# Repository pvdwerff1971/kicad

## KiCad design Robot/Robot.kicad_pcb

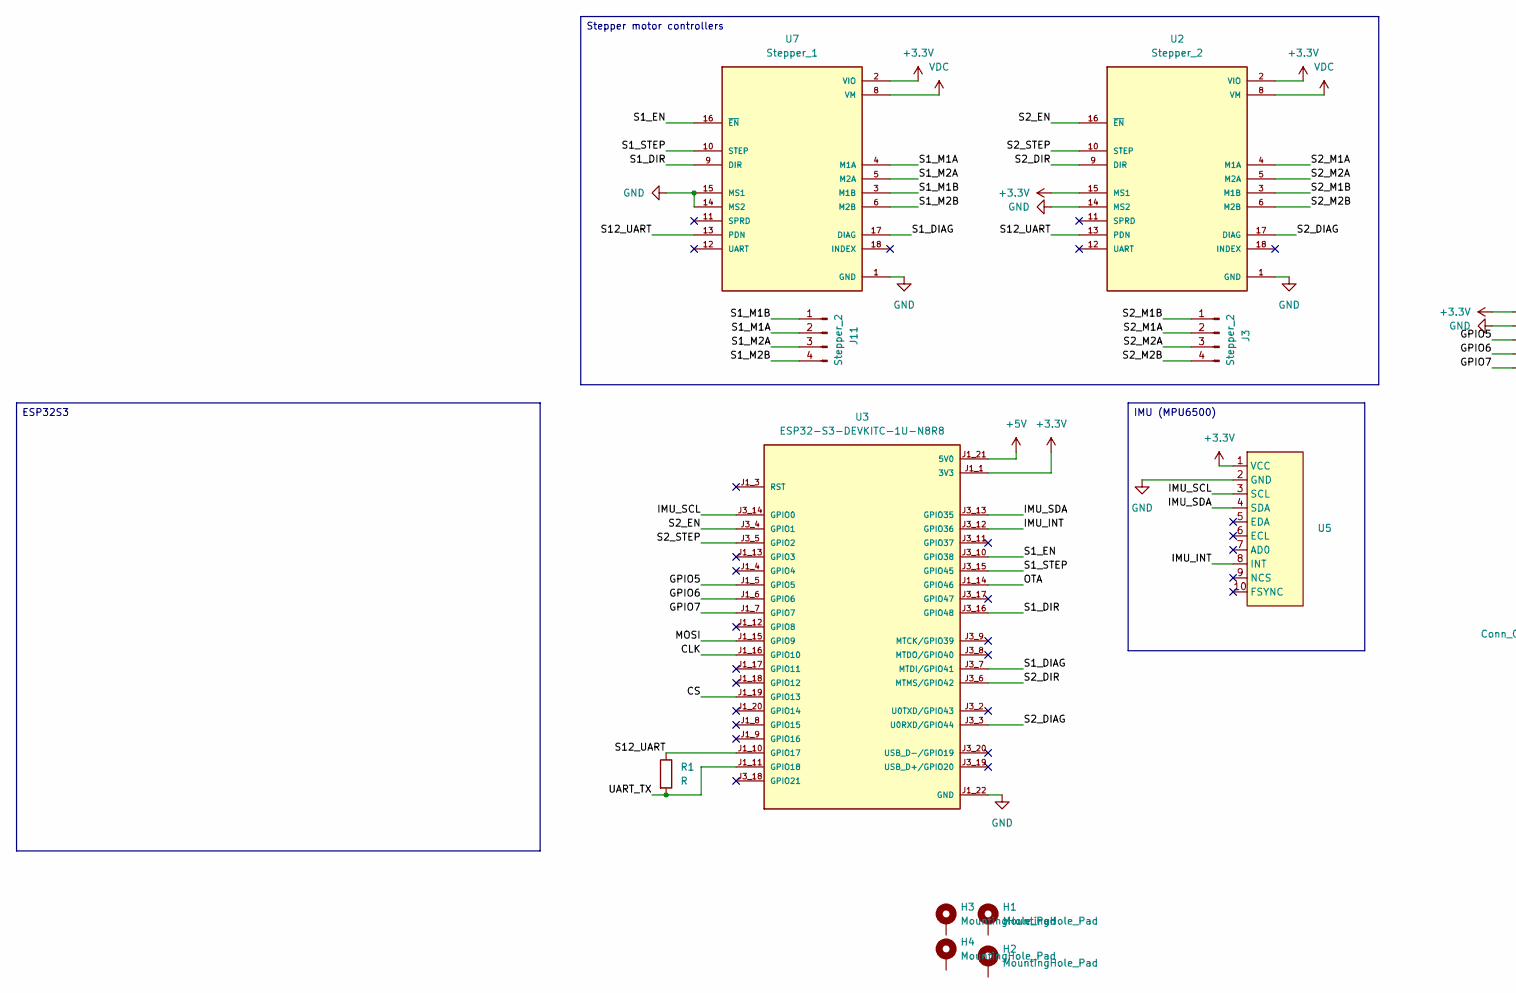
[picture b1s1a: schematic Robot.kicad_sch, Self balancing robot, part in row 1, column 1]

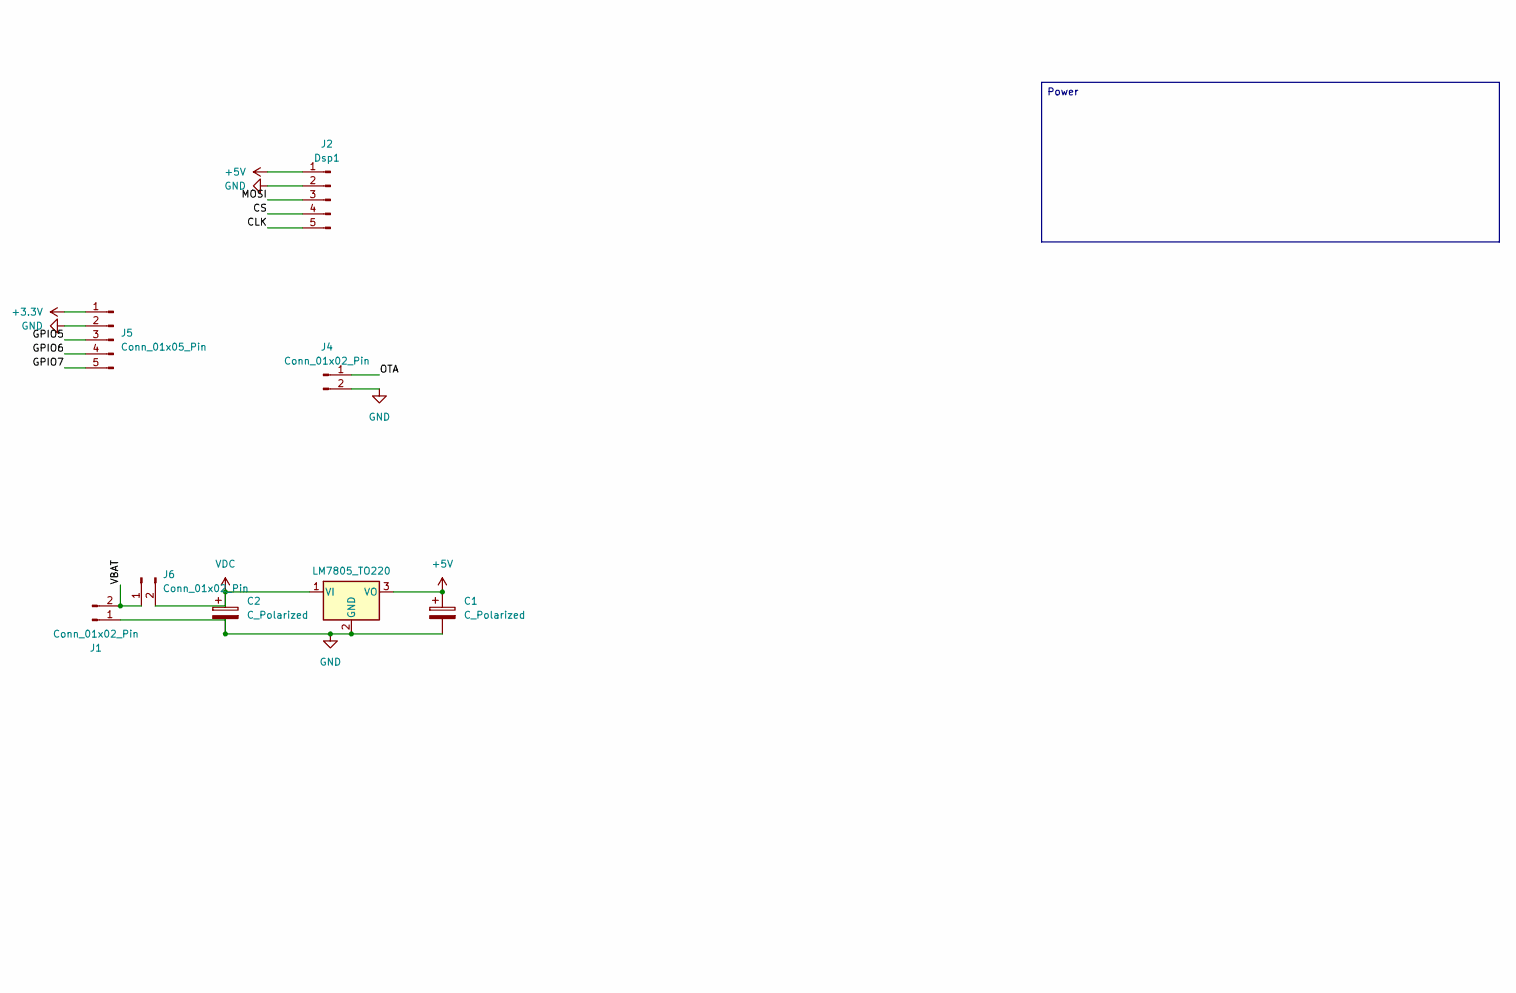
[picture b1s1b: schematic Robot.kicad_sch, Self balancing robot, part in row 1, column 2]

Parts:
C1, C2: C_Polarized; C_Radial_D10.0mm_H20.0mm_P5.00mm
H1, H2, H3, H4: MountingHole_Pad; MountingHole_3.2mm_M3
J1: Conn_01x02_Pin; AMASS_XT60-F_1x02_P7.20mm_Vertical
J2: Dsp1; PinHeader_1x05_P2.54mm_Vertical
J3, J11: Stepper_2; Connector_1x4_p2.54_vertical_stepper
J4, J6: Conn_01x02_Pin; PinHeader_1x02_P2.54mm_Vertical
J5: Conn_01x05_Pin; PinHeader_1x05_P2.54mm_Vertical
R1: R; LED_0805_2012Metric_Pad1.15x1.40mm_HandSolder
U1: LM7805_TO220; TO-220-3_Vertical
U2: Stepper_2; MODULE_TMC2209_SILENTSTEPSTICK; PARTREV 1.20
U3: ESP32-S3-DEVKITC-1U-N8R8; MODULE_ESP32-S3-DEVKITC-1U-N8R8; PARTREV 1.1
U5: MPU6500
U7: Stepper_1; MODULE_TMC2209_SILENTSTEPSTICK; PARTREV 1.20

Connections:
+3.3V: J5.1, U2.2 (VIO), U2.15 (MS1), U3.J1_1 (3V3), U3.J1_2 (3V3), U5.1 (VCC), U7.2 (VIO)
+5V: C1.1, J2.1, U1.3 (VO), U3.J1_21 (5V0)
/CLK: J2.5, U3.J1_16 (GPIO10)
/CS: J2.4, U3.J1_19 (GPIO13)
/GPIO5: J5.3, U3.J1_5 (GPIO5)
/GPIO6: J5.4, U3.J1_6 (GPIO6)
/GPIO7: J5.5, U3.J1_7 (GPIO7)
/IMU_INT: U3.J3_12 (GPIO36), U5.8 (INT)
/IMU_SCL: U3.J3_14 (GPIO0), U5.3 (SCL)
/IMU_SDA: U3.J3_13 (GPIO35), U5.4 (SDA)
/MOSI: J2.3, U3.J1_15 (GPIO9)
/OTA: J4.1, U3.J1_14 (GPIO46)
/S1_DIAG: U3.J3_7 (MTDI/GPIO41), U7.17 (DIAG)
/S1_DIR: U3.J3_16 (GPIO48), U7.9 (DIR)
/S1_EN: U3.J3_10 (GPIO38), U7.16 (~EN)
/S1_M1A: J11.2, U7.4 (M1A)
/S1_M1B: J11.1, U7.3 (M1B)
/S1_M2A: J11.3, U7.5 (M2A)
/S1_M2B: J11.4, U7.6 (M2B)
/S1_STEP: U3.J3_15 (GPIO45), U7.10 (STEP)
/S2_DIAG: U2.17 (DIAG), U3.J3_3 (U0RXD/GPIO44)
/S2_DIR: U2.9 (DIR), U3.J3_6 (MTMS/GPIO42)
/S2_EN: U2.16 (~EN), U3.J3_4 (GPIO1)
/S2_M1A: J3.2, U2.4 (M1A)
/S2_M1B: J3.1, U2.3 (M1B)
/S2_M2A: J3.3, U2.5 (M2A)
/S2_M2B: J3.4, U2.6 (M2B)
/S2_STEP: U2.10 (STEP), U3.J3_5 (GPIO2)
/S12_UART: R1.1, U2.13 (PDN), U3.J1_10 (GPIO17), U7.13 (PDN)
/UART_TX: R1.2, U3.J1_11 (GPIO18)
/VBAT: J1.2, J6.1
GND: C1.2, C2.2, J1.1, J2.2, J4.2, J5.2, U1.2 (GND), U2.1 (GND), U2.7 (GND), U2.14 (MS2), U3.J1_22 (GND), U3.J3_1 (GND), U3.J3_21 (GND), U3.J3_22 (GND), U5.2 (GND), U7.1 (GND), U7.7 (GND), U7.14 (MS2), U7.15 (MS1)
VDC: C2.1, J6.2, U1.1 (VI), U2.8 (VM), U7.8 (VM)

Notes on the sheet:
Stepper motor controllers
Power
IMU (MPU6500)
ESP32S3

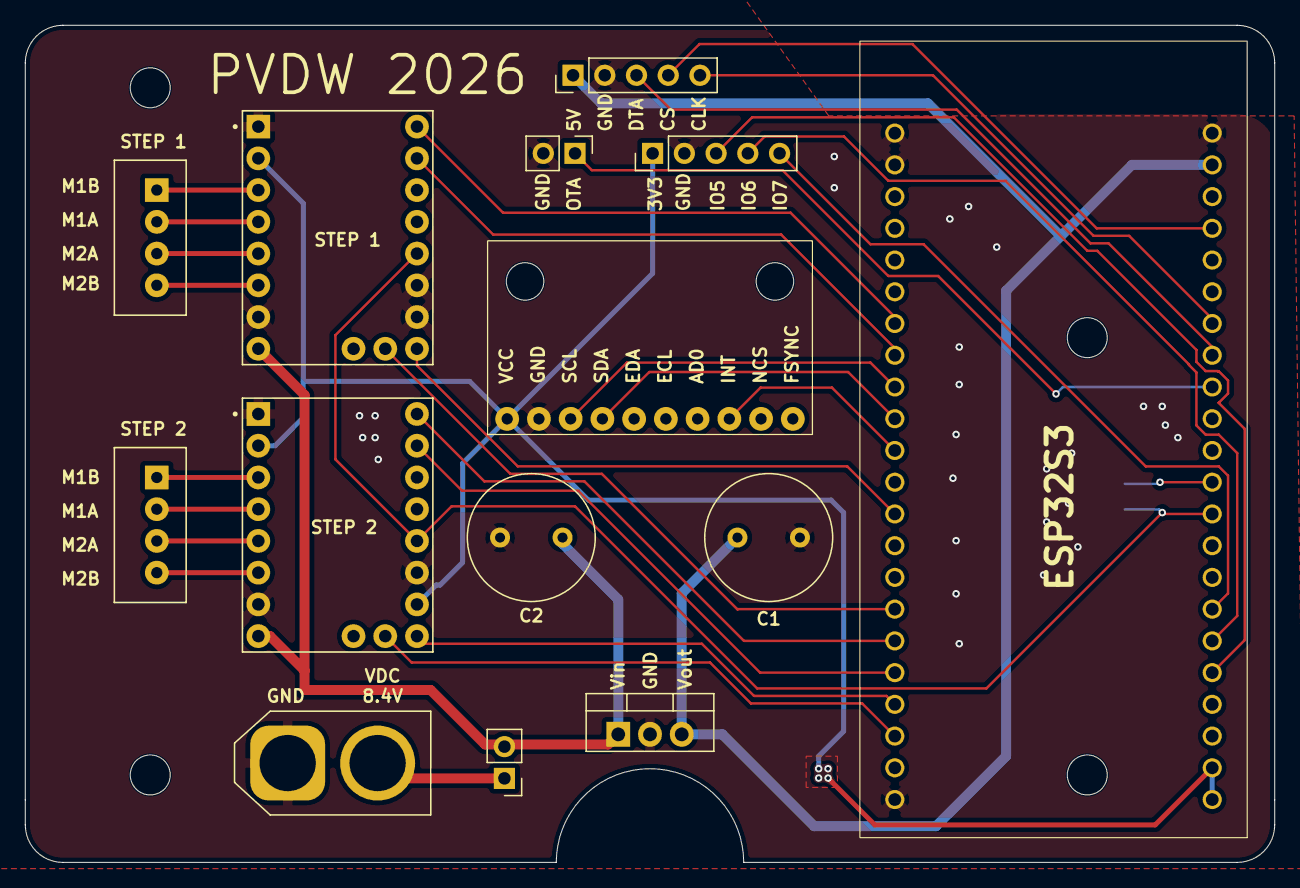
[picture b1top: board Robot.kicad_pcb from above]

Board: 2 copper layers, 100.0 x 67.0 mm, 19 parts (1 on the bottom side), 33 nets.

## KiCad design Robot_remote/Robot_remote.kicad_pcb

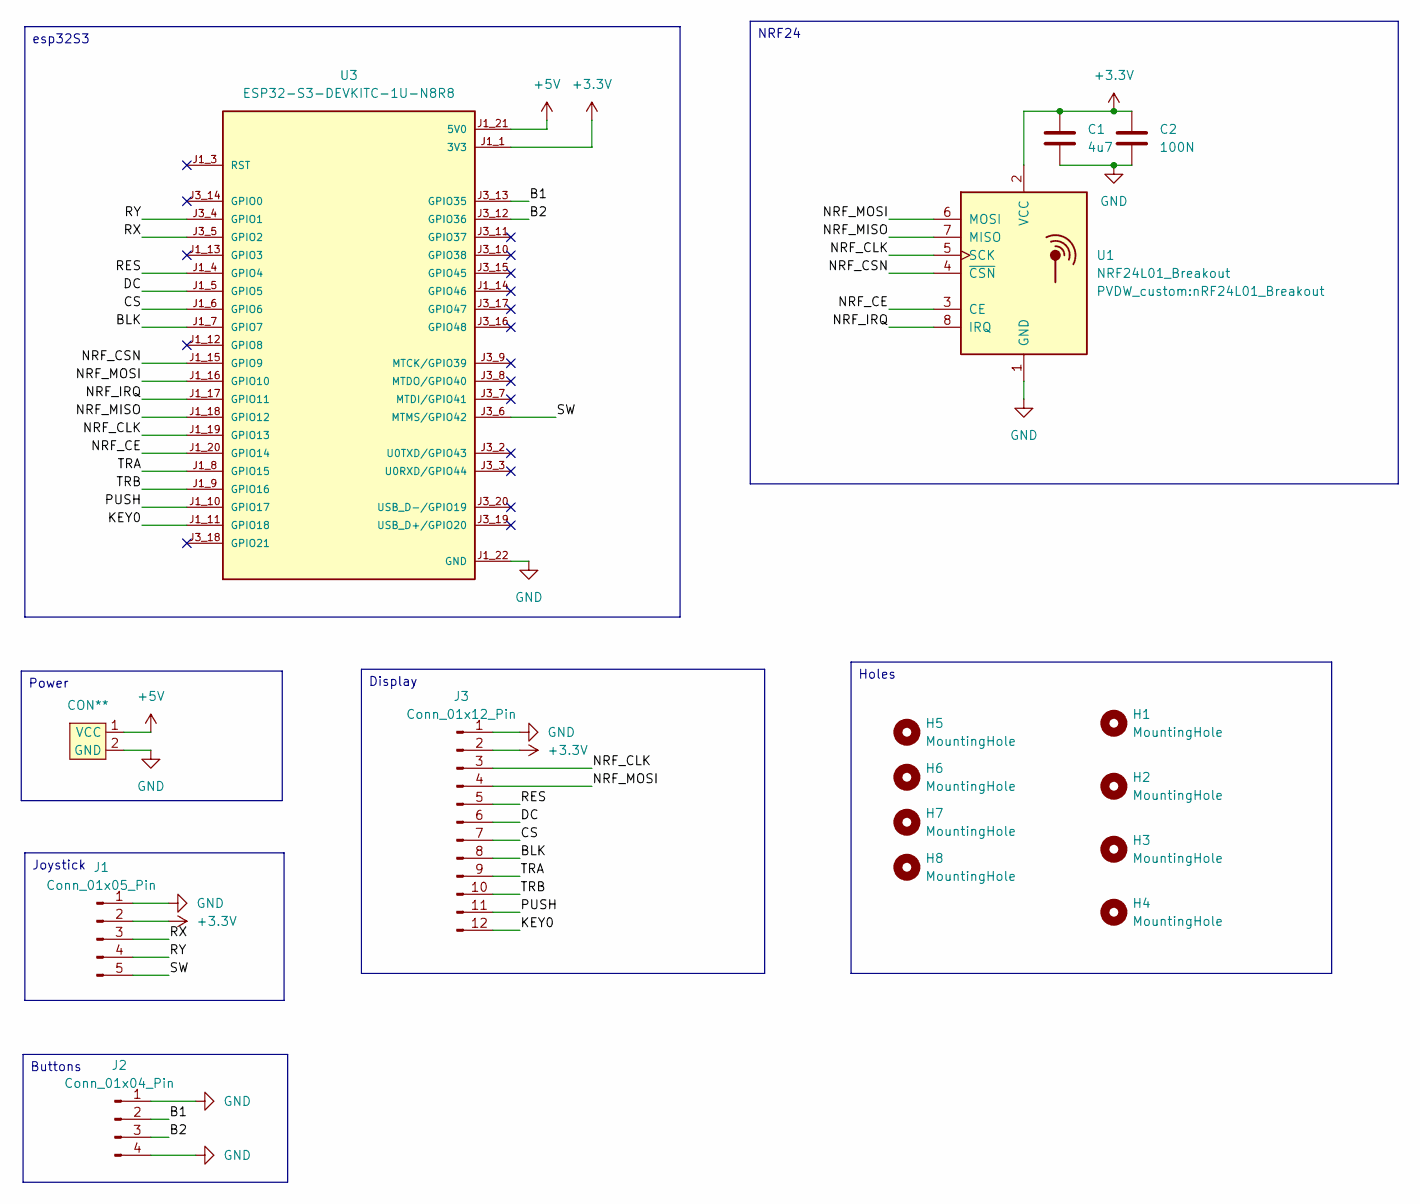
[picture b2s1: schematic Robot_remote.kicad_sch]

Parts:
C1: 4u7; C_0805_2012Metric_Pad1.18x1.45mm_HandSolder
C2: 100N; C_0805_2012Metric_Pad1.18x1.45mm_HandSolder
H1, H2, H3, H4: MountingHole; MountingHole_8.4mm_M8
H5, H6, H7, H8: MountingHole; MountingHole_3.2mm_M3
J1: Conn_01x05_Pin; PinHeader_1x05_P2.54mm_Horizontal
J2: Conn_01x04_Pin; PinHeader_1x04_P2.54mm_Horizontal
J3: Conn_01x12_Pin; PinSocket_1x12_P2.54mm_Vertical
U1: NRF24L01_Breakout; nRF24L01_Breakout
U2: CON**; Connector_1x2_p2.54_horizontal
U3: ESP32-S3-DEVKITC-1U-N8R8; MODULE_ESP32-S3-DEVKITC-1U-N8R8; PARTREV 1.1

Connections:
+3.3V: C1.1, C2.1, J1.2, J3.2, U1.2 (VCC), U3.J1_1 (3V3), U3.J1_2 (3V3)
+5V: U2.1 (VCC), U3.J1_21 (5V0)
/B1: J2.2, U3.J3_13 (GPIO35)
/B2: J2.3, U3.J3_12 (GPIO36)
/BLK: J3.8, U3.J1_7 (GPIO7)
/CS: J3.7, U3.J1_6 (GPIO6)
/DC: J3.6, U3.J1_5 (GPIO5)
/KEY0: J3.12, U3.J1_11 (GPIO18)
/NRF_CE: U1.3 (CE), U3.J1_20 (GPIO14)
/NRF_CLK: J3.3, U1.5 (SCK), U3.J1_19 (GPIO13)
/NRF_CSN: U1.4 (~CSN), U3.J1_15 (GPIO9)
/NRF_IRQ: U1.8 (IRQ), U3.J1_17 (GPIO11)
/NRF_MISO: U1.7 (MISO), U3.J1_18 (GPIO12)
/NRF_MOSI: J3.4, U1.6 (MOSI), U3.J1_16 (GPIO10)
/PUSH: J3.11, U3.J1_10 (GPIO17)
/RES: J3.5, U3.J1_4 (GPIO4)
/RX: J1.3, U3.J3_5 (GPIO2)
/RY: J1.4, U3.J3_4 (GPIO1)
/SW: J1.5, U3.J3_6 (MTMS/GPIO42)
/TRA: J3.9, U3.J1_8 (GPIO15)
/TRB: J3.10, U3.J1_9 (GPIO16)
GND: C1.2, C2.2, J1.1, J2.1, J2.4, J3.1, U1.1 (GND), U2.2 (GND), U3.J1_22 (GND), U3.J3_1 (GND), U3.J3_21 (GND), U3.J3_22 (GND)

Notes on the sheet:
Buttons
Display
esp32S3
Joystick
NRF24
Holes
Power

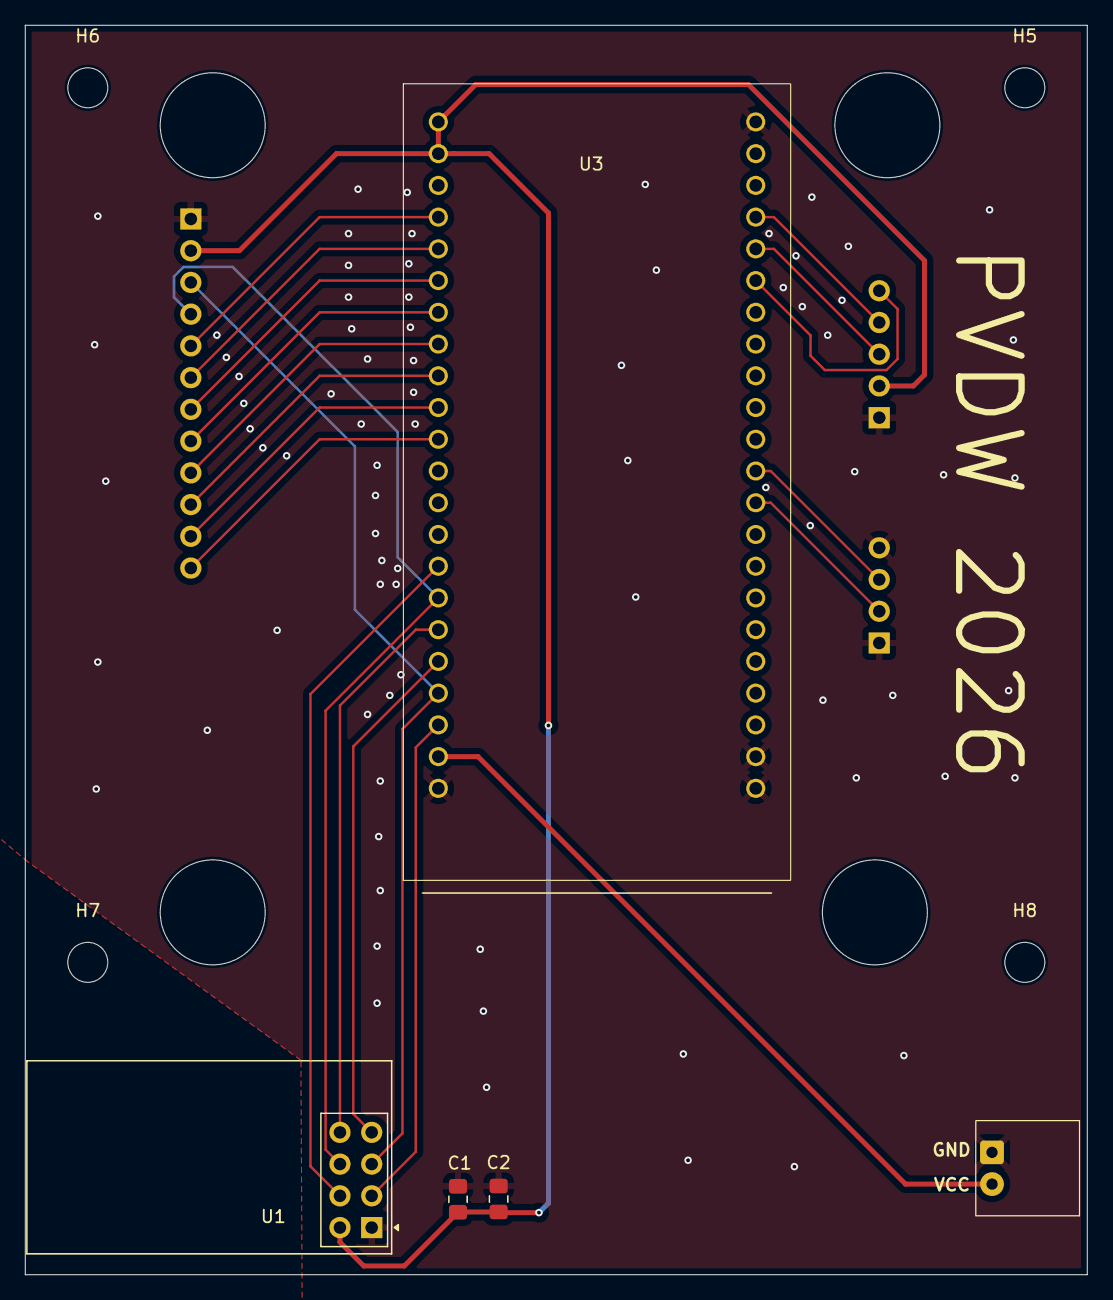
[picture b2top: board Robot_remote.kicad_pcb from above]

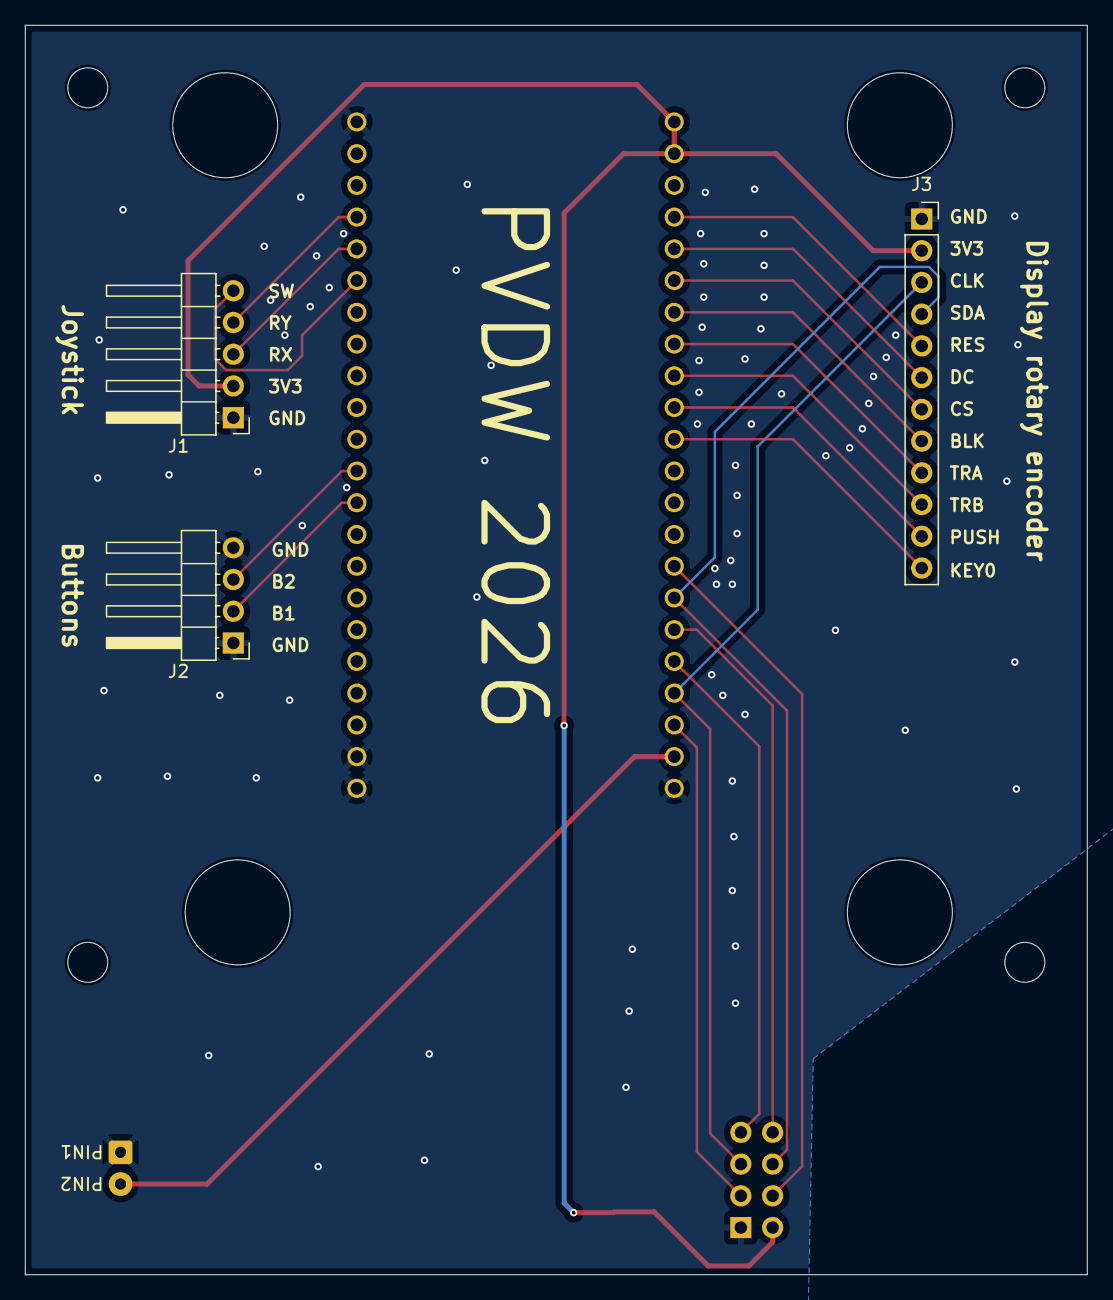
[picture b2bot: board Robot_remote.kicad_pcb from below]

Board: 2 copper layers, 85.0 x 100.0 mm, 16 parts (3 on the bottom side), 22 nets.

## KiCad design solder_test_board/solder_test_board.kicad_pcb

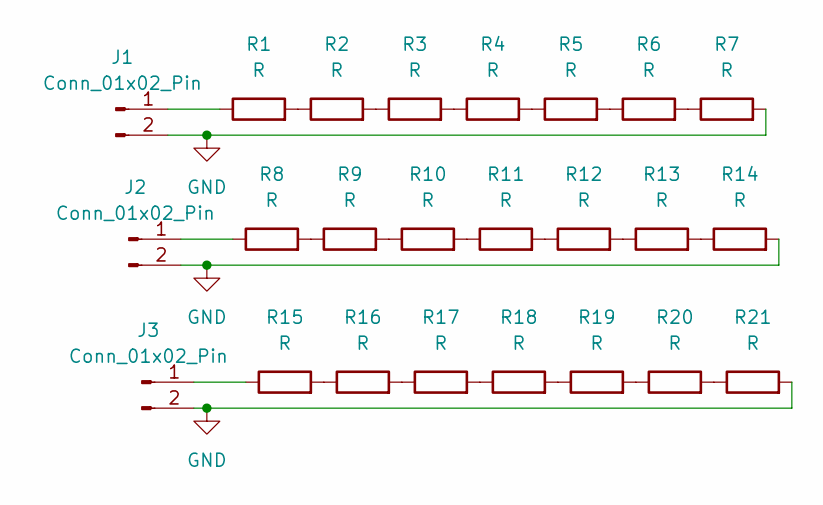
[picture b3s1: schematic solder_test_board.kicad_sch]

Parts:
J1, J2, J3: Conn_01x02_Pin; PinHeader_1x02_P2.54mm_Vertical
R1, R2, R3, R4, R5, R6, R7, R8, R9, R10, R11, R12, R13, R14, R15, R16, R17, R18, R19, R20, R21: R; R_0402_1005Metric

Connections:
GND: J1.2, J2.2, J3.2, R7.2, R14.2, R21.2
unnamed: J1.1, R1.1
unnamed: J2.1, R8.1
unnamed: J3.1, R15.1
unnamed: R1.2, R2.1
unnamed: R2.2, R3.1
unnamed: R3.2, R4.1
unnamed: R4.2, R5.1
unnamed: R5.2, R6.1
unnamed: R6.2, R7.1
unnamed: R8.2, R9.1
unnamed: R9.2, R10.1
unnamed: R10.2, R11.1
unnamed: R11.2, R12.1
unnamed: R12.2, R13.1
unnamed: R13.2, R14.1
unnamed: R15.2, R16.1
unnamed: R16.2, R17.1
unnamed: R17.2, R18.1
unnamed: R18.2, R19.1
unnamed: R19.2, R20.1
unnamed: R20.2, R21.1

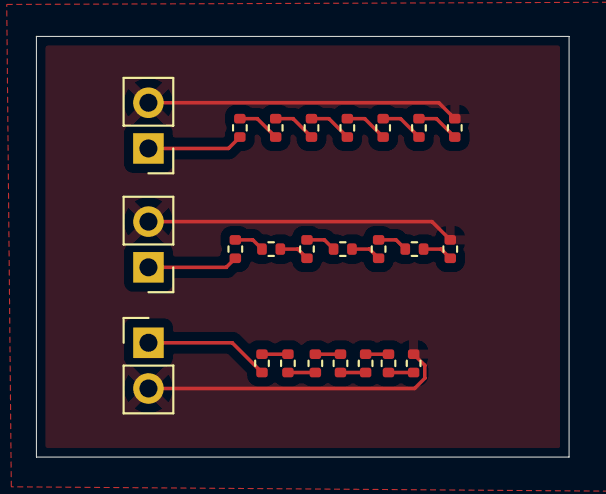
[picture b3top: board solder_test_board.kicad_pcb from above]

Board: 2 copper layers, 29.6 x 23.4 mm, 24 parts (0 on the bottom side), 22 nets.

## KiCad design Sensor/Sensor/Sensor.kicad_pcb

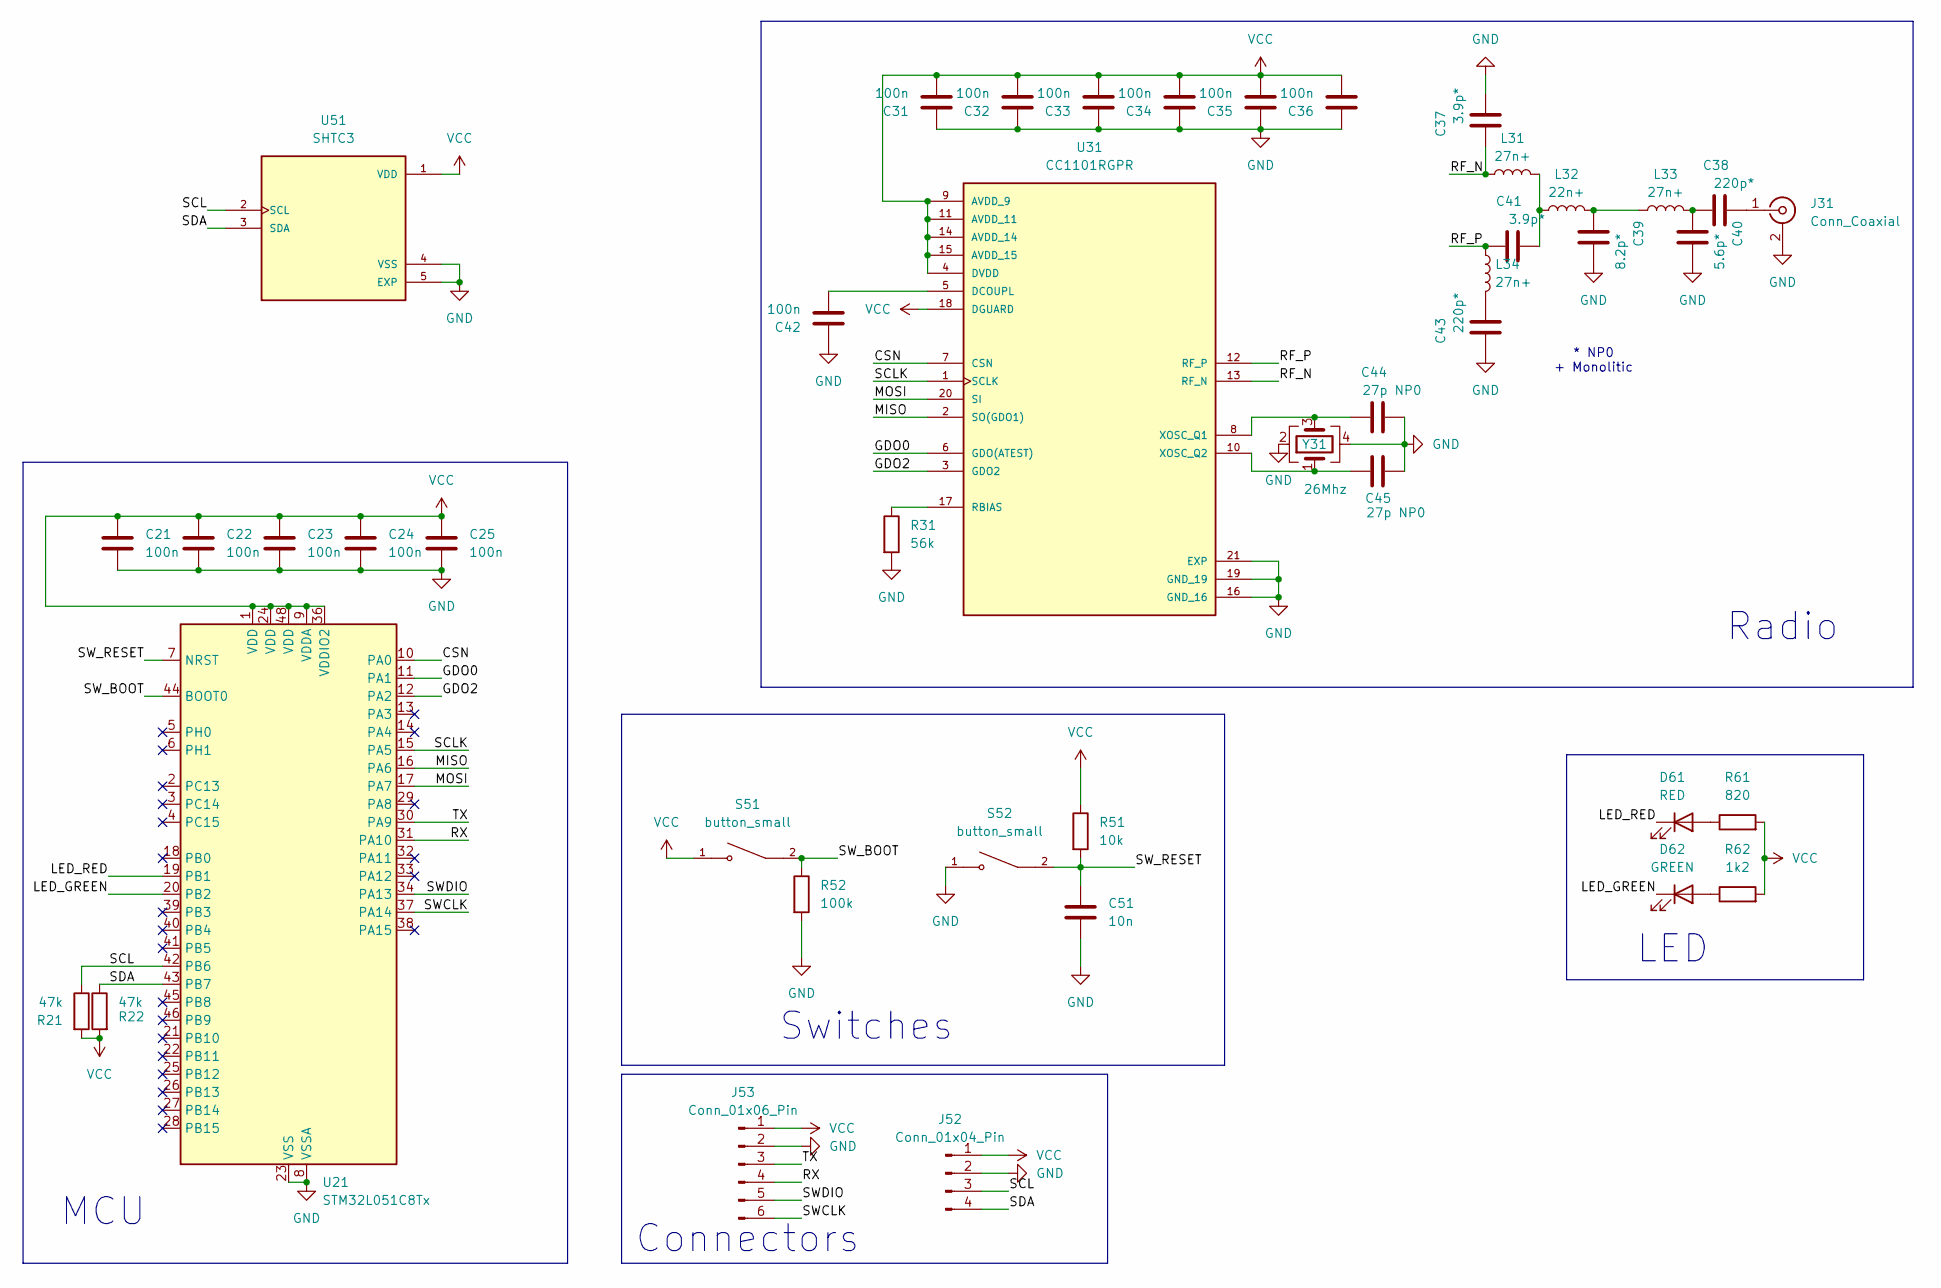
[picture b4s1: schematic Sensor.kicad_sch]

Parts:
C21, C22, C23, C24, C25, C31, C32, C33, C34, C35, C36, C42: 100n; C_0402_1005Metric
C37, C41: 3.9p*; C_0402_1005Metric
C38, C43: 220p*; C_0402_1005Metric
C39: 8.2p*; C_0402_1005Metric
C40: 5.6p*; C_0402_1005Metric
C44, C45: 27p NP0; C_0402_1005Metric
C51: 10n; C_0402_1005Metric
D61: RED; LED_0805_2012Metric
D62: GREEN; LED_0805_2012Metric
J31: Conn_Coaxial; SMA_Amphenol_132289_EdgeMount
J52: Conn_01x04_Pin; PinHeader_1x04_P2.54mm_Vertical
J53: Conn_01x06_Pin; PinSocket_1x06_P2.54mm_Vertical
L31, L33, L34: 27n+; L_0402_1005Metric
L32: 22n+; L_0402_1005Metric
R21, R22: 47k; R_0402_1005Metric
R31: 56k; R_0402_1005Metric
R51: 10k; R_0402_1005Metric
R52: 100k; R_0402_1005Metric
R61: 820; R_0402_1005Metric
R62: 1k2; R_0402_1005Metric
S51, S52: button_small
U21: STM32L051C8Tx; LQFP-48_7x7mm_P0.5mm
U31: CC1101RGPR; QFN-20-1EP_4x4mm_P0.5mm_EP2.5x2.5mm_ThermalVias; PARTREV 6-May-2020
U51: SHTC3; shtc3; PARTREV 3
Y31: 26Mhz; Crystal_SMD_3225-4Pin_3.2x2.5mm

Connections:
/CSN: U21.10 (PA0), U31.7 (CSN)
/GDO0: U21.11 (PA1), U31.6 (GDO(ATEST))
/GDO2: U21.12 (PA2), U31.3 (GDO2)
/LED_GREEN: D62.1 (K), U21.20 (PB2)
/LED_RED: D61.1 (K), U21.19 (PB1)
/MISO: U21.16 (PA6), U31.2 (SO(GDO1))
/MOSI: U21.17 (PA7), U31.20 (SI)
/RF_N: C37.2, L31.1, U31.13 (RF_N)
/RF_P: C41.2, L34.1, U31.12 (RF_P)
/RX: J53.4, U21.31 (PA10)
/SCL: J52.3, R21.1, U21.42 (PB6), U51.2 (SCL)
/SCLK: U21.15 (PA5), U31.1 (SCLK)
/SDA: J52.4, R22.1, U21.43 (PB7), U51.3 (SDA)
/SWCLK: J53.6, U21.37 (PA14)
/SWDIO: J53.5, U21.34 (PA13)
/SW_BOOT: R52.1, S51.2, U21.44 (BOOT0)
/SW_RESET: C51.1, R51.2, S52.2, U21.7 (NRST)
/TX: J53.3, U21.30 (PA9)
GND: C21.2, C22.2, C23.2, C24.2, C25.2, C31.1, C32.1, C33.1, C34.1, C35.1, C36.1, C37.1, C39.1, C40.1, C42.1, C43.2, C44.1, C45.1, C51.2, J31.2 (Ext), J52.2, J53.2, R31.2, R52.2, S52.1, U21.8 (VSSA), U21.23 (VSS), U21.35 (VSS), U21.47 (VSS), U31.16 (GND_16), U31.19 (GND_19), U31.21 (EXP), U51.4 (VSS), U51.5 (EXP), Y31.2, Y31.4
unnamed: C38.2, C40.2, L33.2
unnamed: C39.2, L32.2, L33.1
unnamed: C41.1, L31.2, L32.1
unnamed: C43.1, L34.2
unnamed: D61.2 (A), R61.1
unnamed: D62.2 (A), R62.1
unnamed: C38.1, J31.1 (In)
unnamed: C42.2, U31.5 (DCOUPL)
unnamed: R31.1, U31.17 (RBIAS)
unnamed: C44.2, U31.8 (XOSC_Q1), Y31.3
unnamed: C45.2, U31.10 (XOSC_Q2), Y31.1
VCC: C21.1, C22.1, C23.1, C24.1, C25.1, C31.2, C32.2, C33.2, C34.2, C35.2, C36.2, J52.1, J53.1, R21.2, R22.2, R51.1, R61.2, R62.2, S51.1, U21.1 (VDD), U21.9 (VDDA), U21.24 (VDD), U21.36 (VDDIO2), U21.48 (VDD), U31.4 (DVDD), U31.9 (AVDD_9), U31.11 (AVDD_11), U31.14 (AVDD_14), U31.15 (AVDD_15), U31.18 (DGUARD), U51.1 (VDD)

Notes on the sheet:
Switches
Radio
Connectors
MCU
* NP0 + Monolitic
LED

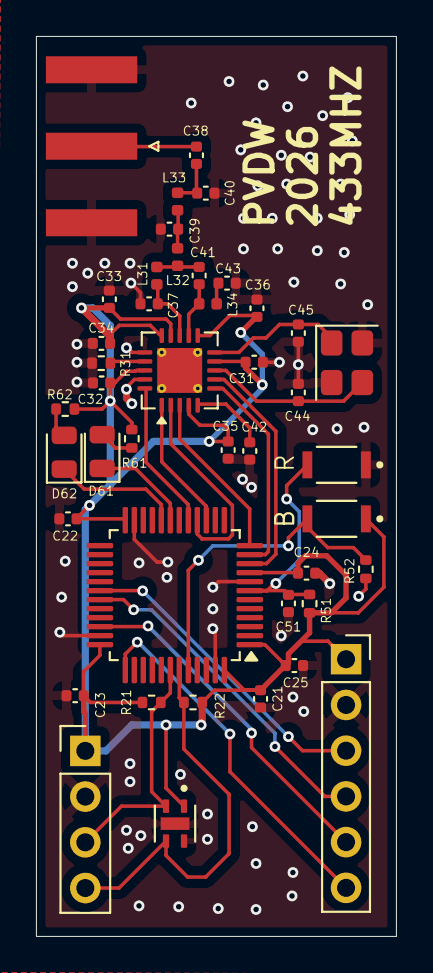
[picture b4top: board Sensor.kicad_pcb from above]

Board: 2 copper layers, 20.0 x 50.0 mm, 43 parts (0 on the bottom side), 31 nets.

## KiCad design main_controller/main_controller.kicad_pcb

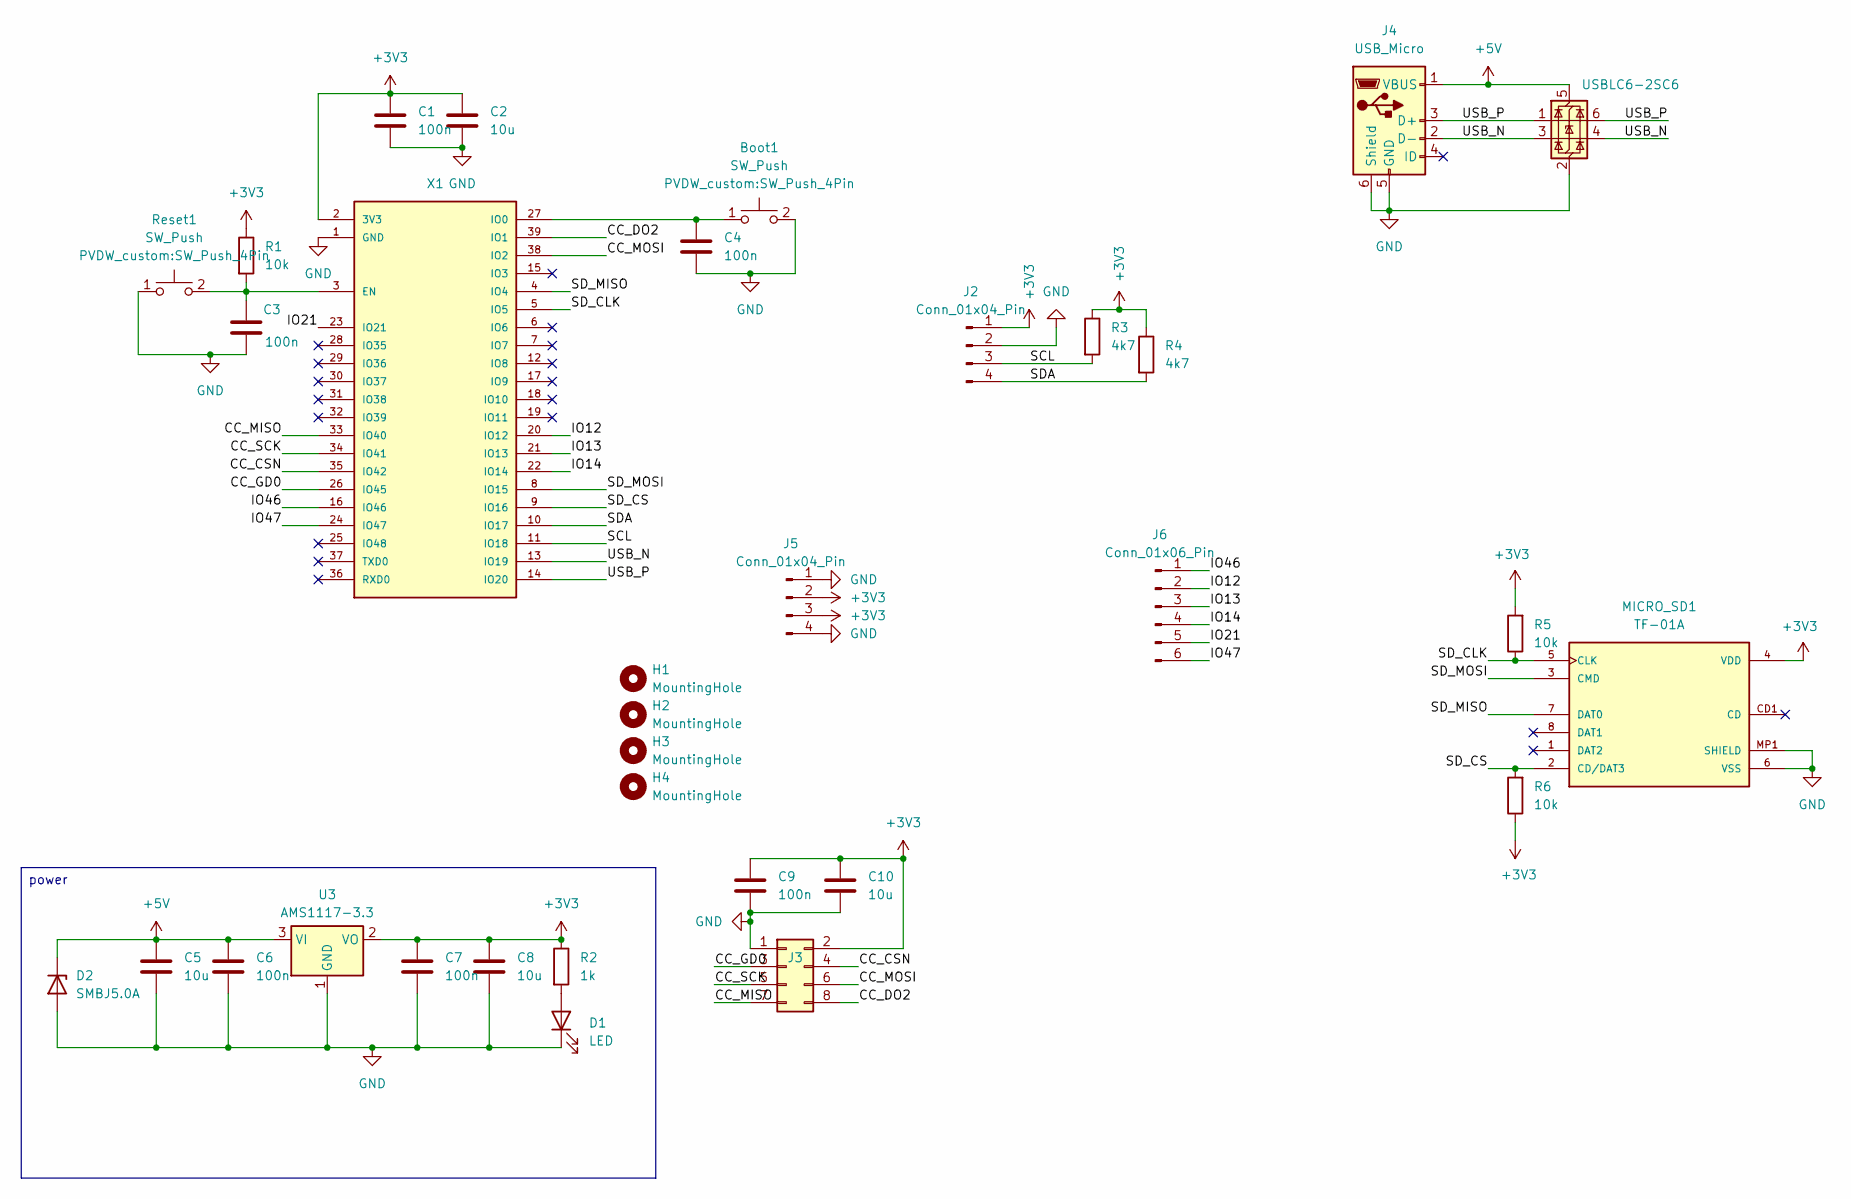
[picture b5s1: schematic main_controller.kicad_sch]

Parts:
Boot1: SW_Push; SW_Push_4Pin
C1, C3, C4, C6, C7, C9: 100n; C_0805_2012Metric
C2, C5, C8, C10: 10u; C_0805_2012Metric
D1: LED; LED_0805_2012Metric
D2: SMBJ5.0A; D_SMB
H1, H2, H3, H4: MountingHole; MountingHole_2.2mm_M2_DIN965
J2: Conn_01x04_Pin; PinSocket_1x04_P2.54mm_Vertical
J3: Conn_02x04_Odd_Even; PinHeader_2x04_P2.54mm_Vertical
J4: USB_Micro; USB_Micro_type3
J5: Conn_01x04_Pin; PinHeader_1x04_P2.54mm_Vertical
J6: Conn_01x06_Pin; PinHeader_1x06_P2.54mm_Vertical
MICRO_SD1: TF-01A
R1, R5, R6: 10k; R_0805_2012Metric
R2: 1k; R_0805_2012Metric
R3, R4: 4k7; R_0805_2012Metric
Reset1: SW_Push; SW_Push_4Pin
U1: USBLC6-2SC6; SOT-23-6
U3: AMS1117-3.3; SOT-223-3_TabPin2
X1: ESP32-S3-WROOM-1-N16R8; ESP32-S3-WROOM-1U; MANUFACTURER_PART_NUMBER ESP32-S3-WROOM-1-N16R8

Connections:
+3V3: C1.1, C2.1, C7.1, C8.1, C9.2, C10.1, J2.1, J3.2, J5.2, J5.3, MICRO_SD1.4 (VDD), R1.1, R2.1, R3.1, R4.1, R5.2, R6.1, U3.2 (VO), X1.2 (3V3)
+5V: C5.1, C6.1, D2.1 (K), J4.1 (VBUS), U1.5 (VBUS), U3.3 (VI)
/CC_CSN: J3.4, X1.35 (IO42)
/CC_DO2: J3.8, X1.39 (IO1)
/CC_GD0: J3.3, X1.26 (IO45)
/CC_MISO: J3.7, X1.33 (IO40)
/CC_MOSI: J3.6, X1.38 (IO2)
/CC_SCK: J3.5, X1.34 (IO41)
/IO12: J6.2, X1.20 (IO12)
/IO13: J6.3, X1.21 (IO13)
/IO14: J6.4, X1.22 (IO14)
/IO21: J6.5, X1.23 (IO21)
/IO46: J6.1, X1.16 (IO46)
/IO47: J6.6, X1.24 (IO47)
/SCL: J2.3, R3.2, X1.11 (IO18)
/SDA: J2.4, R4.2, X1.10 (IO17)
/SD_CLK: MICRO_SD1.5 (CLK), R5.1, X1.5 (IO5)
/SD_CS: MICRO_SD1.2 (CD/DAT3), R6.2, X1.9 (IO16)
/SD_MISO: MICRO_SD1.7 (DAT0), X1.4 (IO4)
/SD_MOSI: MICRO_SD1.3 (CMD), X1.8 (IO15)
/USB_N: J4.2 (D-), U1.3 (I/O2), U1.4 (I/O2), X1.13 (IO19)
/USB_P: J4.3 (D+), U1.1 (I/O1), U1.6 (I/O1), X1.14 (IO20)
GND: Boot1.2, C1.2, C2.2, C3.2, C4.2, C5.2, C6.2, C7.2, C8.2, C9.1, C10.2, D1.1 (K), D2.2 (A), J2.2, J3.1, J4.5 (GND), J4.6 (Shield), J5.1, J5.4, MICRO_SD1.6 (VSS), MICRO_SD1.MP1 (SHIELD), MICRO_SD1.MP2 (SHIELD), MICRO_SD1.MP3 (SHIELD), MICRO_SD1.MP4 (SHIELD), Reset1.1, U1.2 (GND), U3.1 (GND), X1.1 (GND), X1.40 (GND), X1.41 (GND), X1.42 (GND), X1.43 (GND), X1.44 (GND), X1.45 (GND), X1.46 (GND), X1.47 (GND), X1.48 (GND), X1.49 (GND)
unnamed: D1.2 (A), R2.2
unnamed: C3.1, R1.2, Reset1.2, X1.3 (EN)
unnamed: Boot1.1, C4.1, X1.27 (IO0)

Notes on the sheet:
power

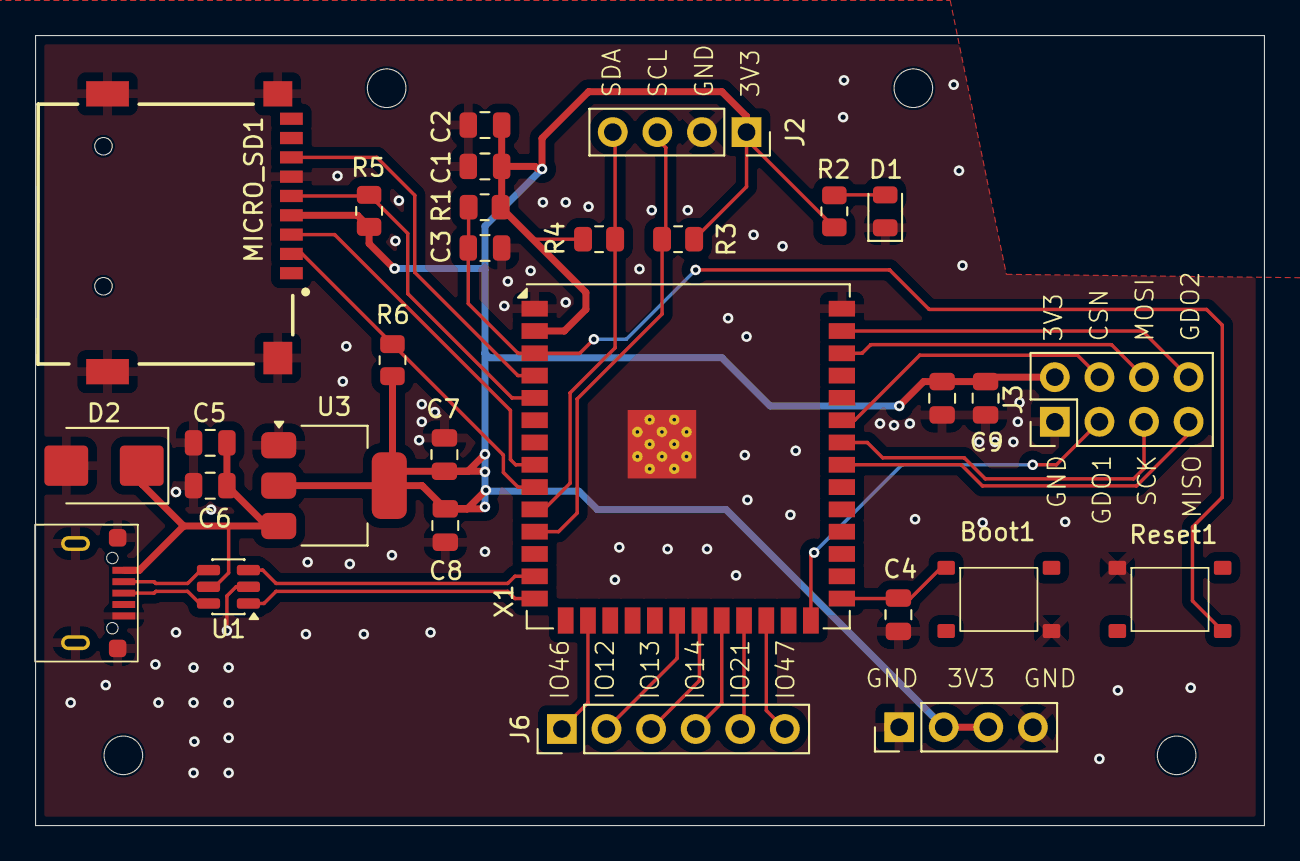
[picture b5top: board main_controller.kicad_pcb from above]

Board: 2 copper layers, 70.0 x 45.0 mm, 33 parts (0 on the bottom side), 26 nets.
